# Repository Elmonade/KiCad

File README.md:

Hitbox style leverless controller. 

Intended to be used with hot-swappable sockets.

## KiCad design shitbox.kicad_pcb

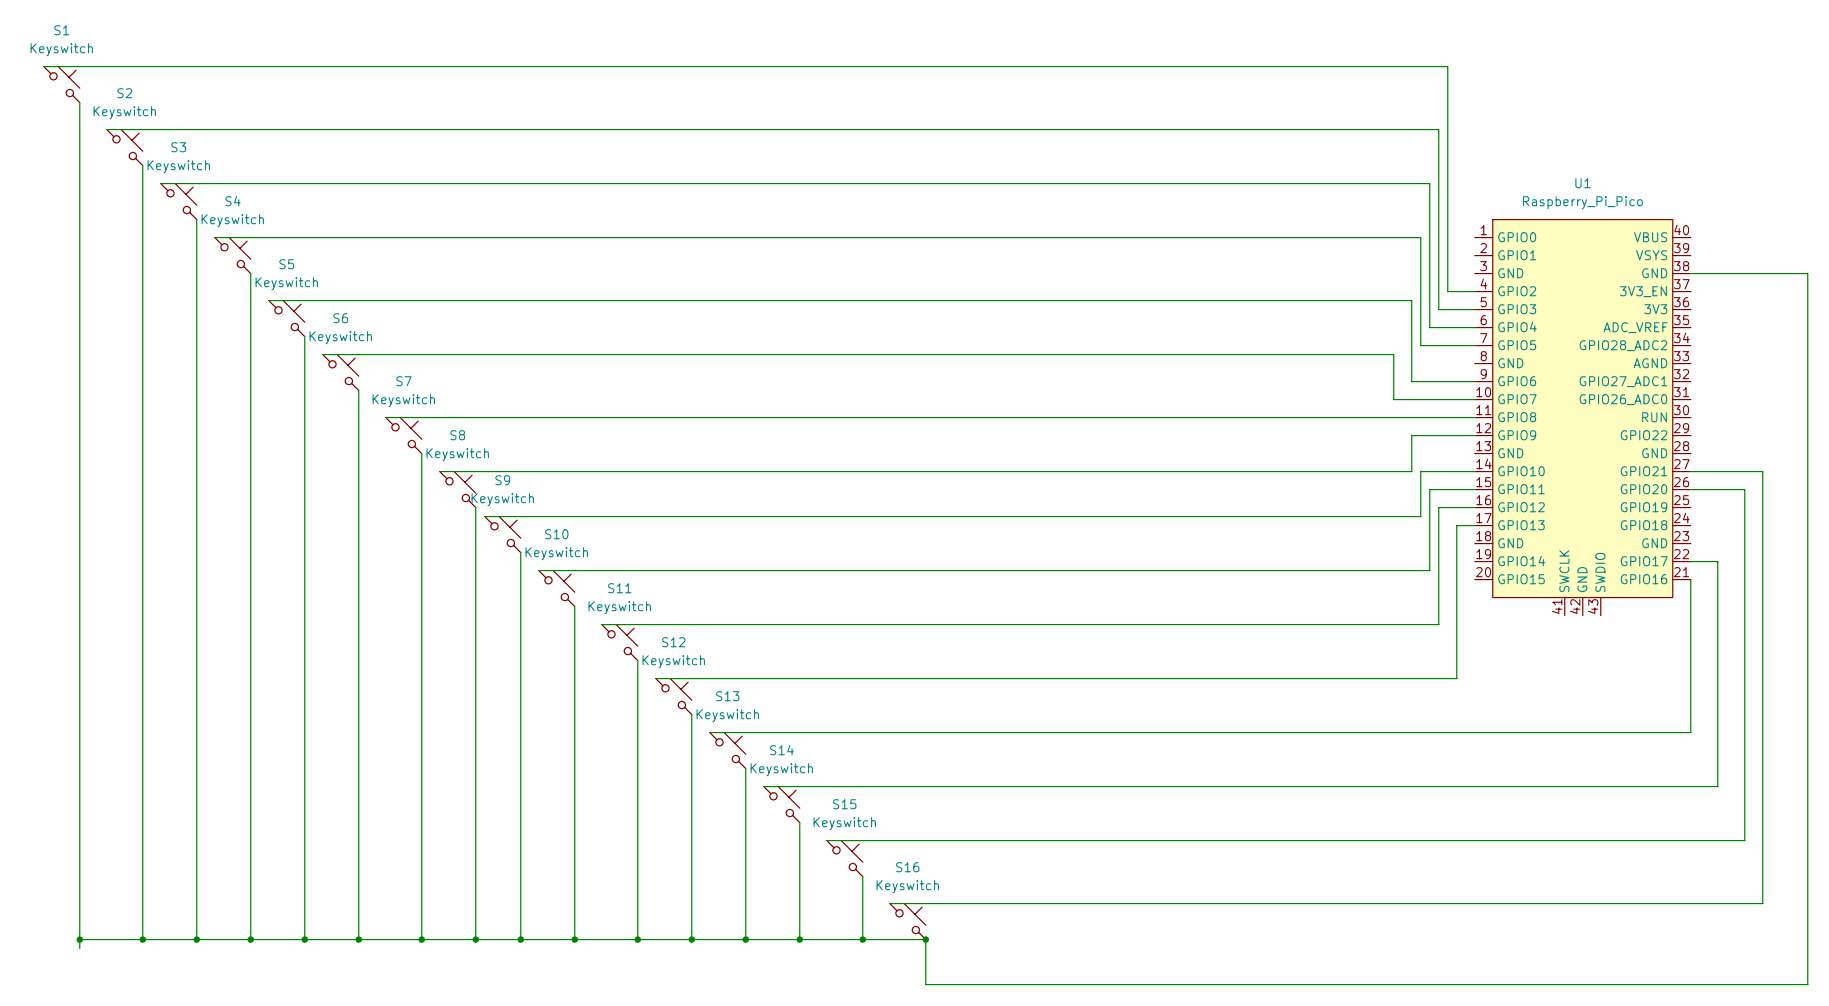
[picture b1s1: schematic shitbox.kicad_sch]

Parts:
S1, S2, S3, S4, S5, S6, S7, S8, S9, S10, S11, S12: Keyswitch; SW_Hotswap_Kailh_MX
S13, S14, S15, S16: Keyswitch; SW_PUSH_6mm
U1: Raspberry_Pi_Pico; raspberry_pi_pico_THT

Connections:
unnamed: S1.2, S2.2, S3.2, S4.2, S5.2, S6.2, S7.2, S8.2, S9.2, S10.2, S11.2, S12.2, S13.2, S14.2, S15.2, S16.2, U1.38 (GND)
unnamed: S1.1, U1.4 (GPIO2)
unnamed: S2.1, U1.5 (GPIO3)
unnamed: S3.1, U1.6 (GPIO4)
unnamed: S4.1, U1.7 (GPIO5)
unnamed: S5.1, U1.9 (GPIO6)
unnamed: S6.1, U1.10 (GPIO7)
unnamed: S7.1, U1.11 (GPIO8)
unnamed: S8.1, U1.12 (GPIO9)
unnamed: S9.1, U1.14 (GPIO10)
unnamed: S10.1, U1.15 (GPIO11)
unnamed: S11.1, U1.16 (GPIO12)
unnamed: S12.1, U1.17 (GPIO13)
unnamed: S13.1, U1.21 (GPIO16)
unnamed: S14.1, U1.22 (GPIO17)
unnamed: S15.1, U1.26 (GPIO20)
unnamed: S16.1, U1.27 (GPIO21)

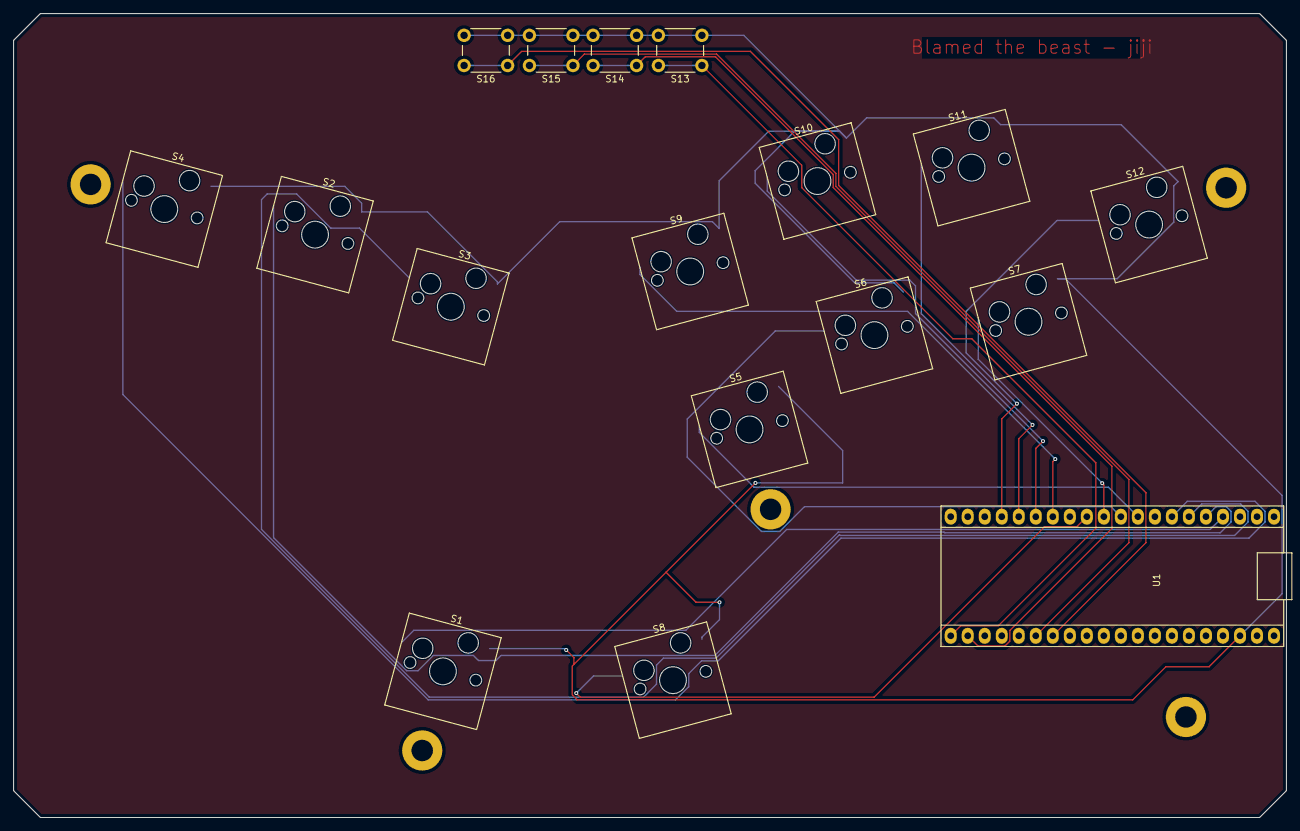
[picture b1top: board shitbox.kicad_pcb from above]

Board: 2 copper layers, 190.0 x 120.0 mm, 17 parts (0 on the bottom side), 17 nets.

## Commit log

2025-04-11 Leverless controller design.
2025-04-12 Happy with the positioning of the buttons. Now to updating the wiring.
2025-04-13 Done.
2025-04-13 Kicad, please don't crash...
